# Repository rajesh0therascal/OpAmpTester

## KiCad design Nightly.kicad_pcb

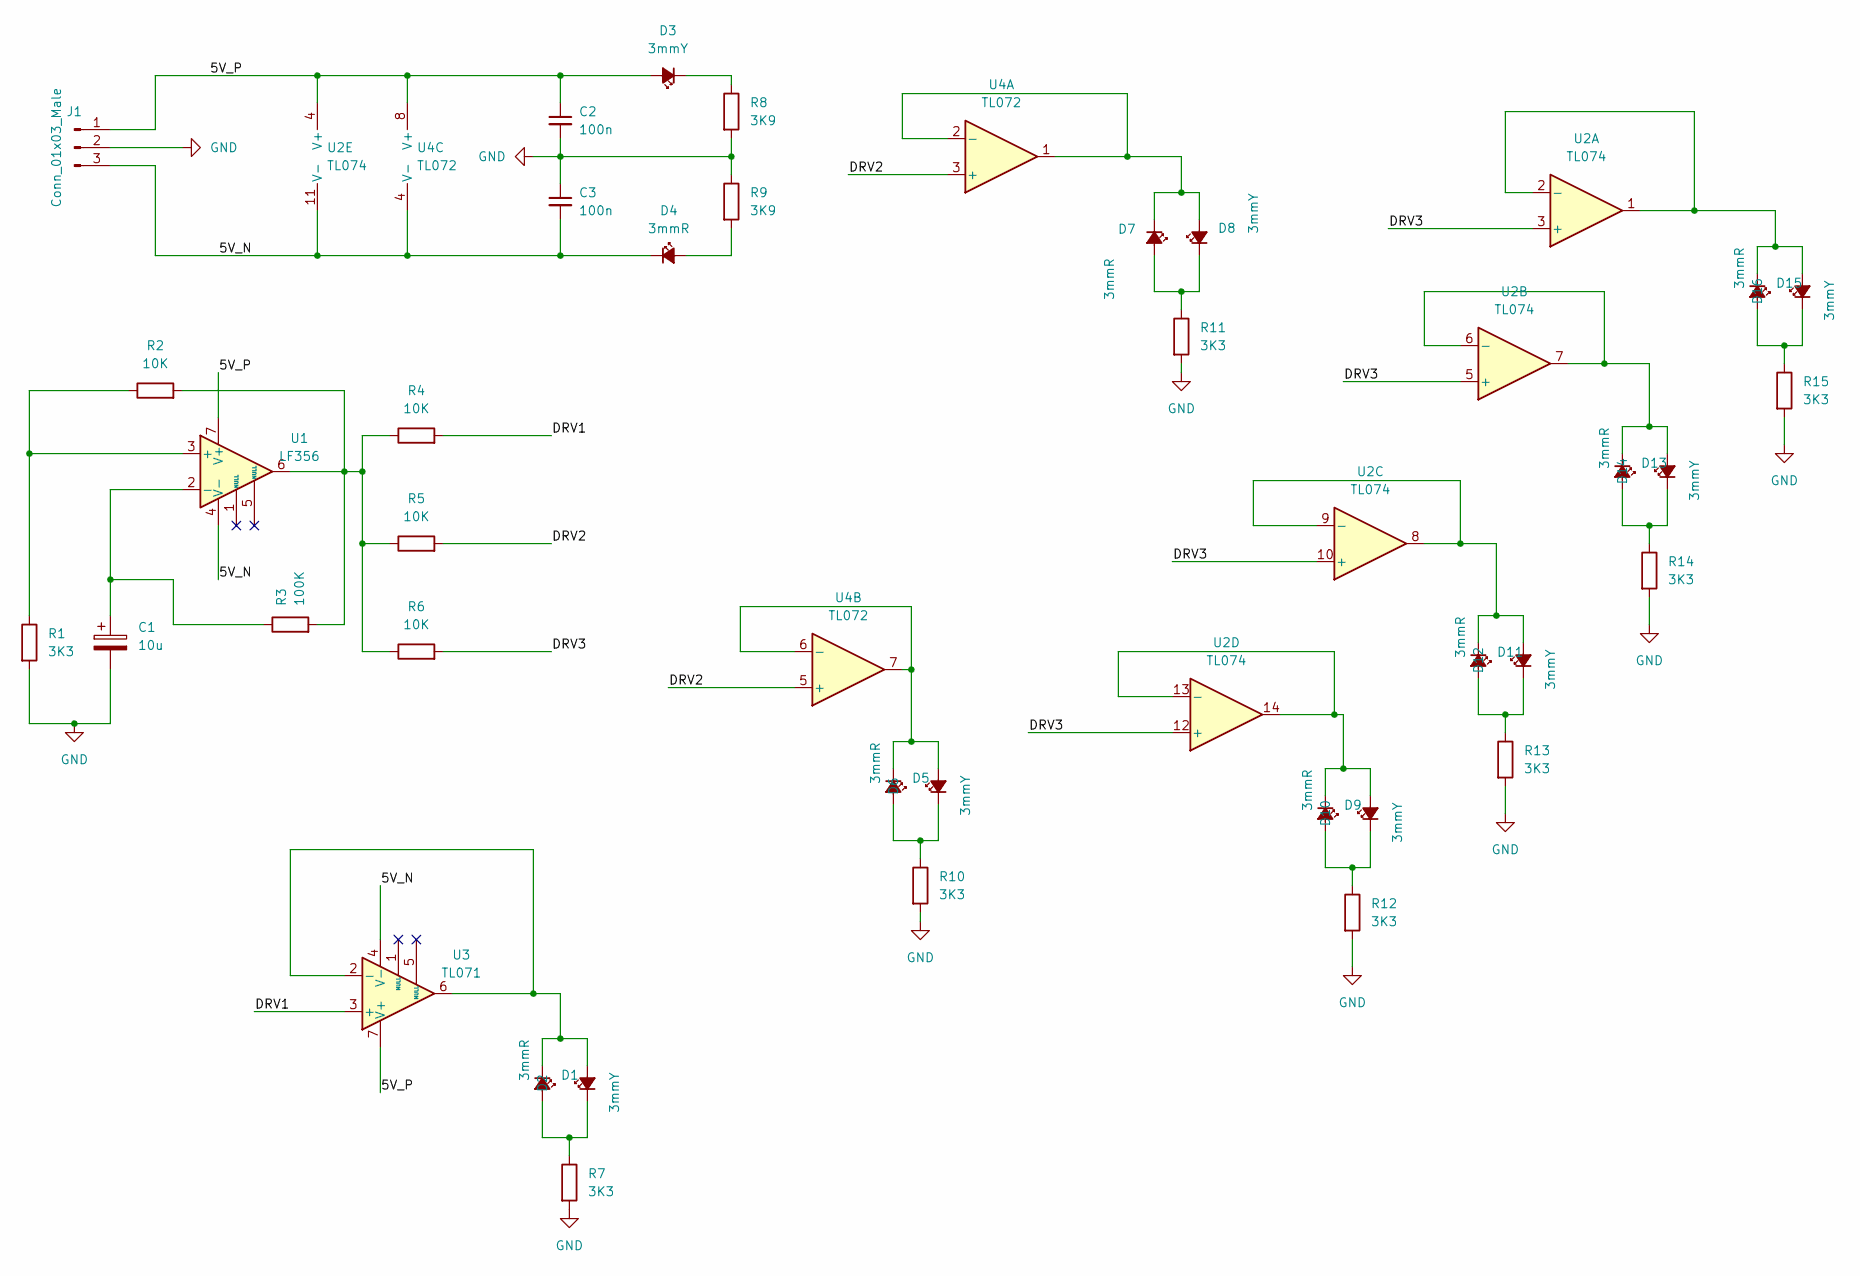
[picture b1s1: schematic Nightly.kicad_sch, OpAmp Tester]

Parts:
C1: 10u; CP_Radial_D5.0mm_P2.50mm
C2, C3: 100n; CP_Radial_D5.0mm_P2.50mm
D1, D4, D5, D7, D9, D11, D13, D15: 3mmR; LED_D3.0mm
D2, D3, D6, D8, D10, D12, D14, D16: 3mmY; LED_D3.0mm
J1: Conn_01x03_Male; PhoenixContact_MSTBA_2,5_3-G-5,08_1x03_P5.08mm_Horizontal
R1, R7, R10, R11, R12, R13, R14, R15: 3K3; R_Axial_DIN0411_L9.9mm_D3.6mm_P15.24mm_Horizontal
R2, R4, R5, R6: 10K; R_Axial_DIN0411_L9.9mm_D3.6mm_P15.24mm_Horizontal
R3: 100K; R_Axial_DIN0411_L9.9mm_D3.6mm_P15.24mm_Horizontal
R8, R9: 3K9; R_Axial_DIN0411_L9.9mm_D3.6mm_P15.24mm_Horizontal
U1: LF356; DIP-8_W7.62mm_Socket
U2: TL074; DIP-16_W7.62mm_Socket
U3: TL071; DIP-8_W7.62mm_Socket
U4: TL072; DIP-8_W7.62mm_Socket

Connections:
/5V_N: C3.2, D4.1 (K), J1.3, U1.4 (V-), U2.11 (V-), U3.4 (V-), U4.4 (V-)
/5V_P: C2.1, D3.2 (A), J1.1, U1.7 (V+), U2.4 (V+), U3.7 (V+), U4.8 (V+)
/DRV1: R4.2, U3.3 (+)
/DRV2: R5.2, U4.3 (+), U4.5 (+)
/DRV3: R6.2, U2.3 (+), U2.5 (+), U2.10 (+), U2.12 (+)
GND: C1.2, C2.2, C3.1, J1.2, R1.2, R7.2, R8.2, R9.1, R10.2, R11.2, R12.2, R13.2, R14.2, R15.2
unnamed: C1.1, R3.1, U1.2 (-)
unnamed: D1.1 (K), D2.2 (A), U3.2 (-), U3.6
unnamed: D1.2 (A), D2.1 (K), R7.1
unnamed: D3.1 (K), R8.1
unnamed: D4.2 (A), R9.2
unnamed: D5.1 (K), D6.2 (A), U4.6 (-), U4.7
unnamed: D5.2 (A), D6.1 (K), R10.1
unnamed: D7.1 (K), D8.2 (A), U4.1, U4.2 (-)
unnamed: D7.2 (A), D8.1 (K), R11.1
unnamed: D9.2 (A), D10.1 (K), R12.1
unnamed: D9.1 (K), D10.2 (A), U2.13 (-), U2.14
unnamed: D11.1 (K), D12.2 (A), U2.8, U2.9 (-)
unnamed: D11.2 (A), D12.1 (K), R13.1
unnamed: D13.1 (K), D14.2 (A), U2.6 (-), U2.7
unnamed: D13.2 (A), D14.1 (K), R14.1
unnamed: D15.1 (K), D16.2 (A), U2.1, U2.2 (-)
unnamed: D15.2 (A), D16.1 (K), R15.1
unnamed: R1.1, R2.1, U1.3 (+)
unnamed: R2.2, R3.2, R4.1, R5.1, R6.1, U1.6

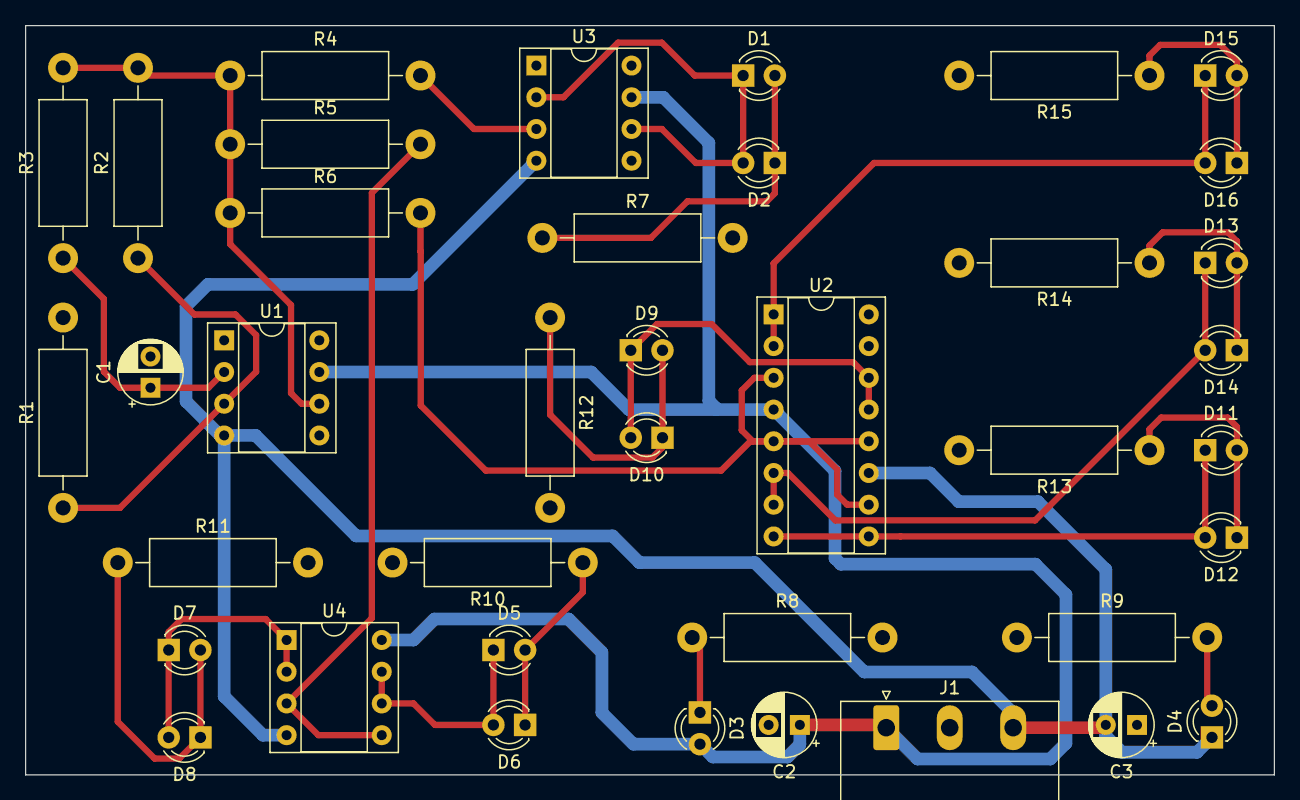
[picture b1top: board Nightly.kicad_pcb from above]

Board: 2 copper layers, 100.0 x 60.0 mm, 39 parts (0 on the bottom side), 25 nets.

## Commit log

2024-03-07 Initial Upload
